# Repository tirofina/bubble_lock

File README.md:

# bubble_lock

Privacy Bubble의 CORE, 정책·MEC·handover·FL·MCP 통합 서비스, ESP32-S3 키링, Raspberry Pi Gateway, 웹 대시보드를 묶은 저장소입니다.

시작 화면에서 사용자 대시보드와 운영 대시보드로 진입합니다. 사용자 화면은 가족·키링 등록, 사건별 위치 공유 승인, 동의·권한 회수, 명령 승인, 알림을 제공합니다. 지도는 GPS/MEC 핀, 위치 정확도 원, 수신기 중심 BLE 추정 원을 표시하며 키링별로 선택할 수 있습니다. 모의 관측과 실제 연결의 출처·관측 시각을 화면에 표시합니다.

## 통합 브랜치

`codex/integrate-all-branches`에서 다음 원격 브랜치의 전체 이력을 통합했습니다. 각 원본은 로컬 추적 브랜치와 `origin/*`에 보관합니다.

| 브랜치 | 원본 커밋 | 구성 |
|---|---|---|
| `main` | `d54a43a` | CORE·중앙 통합 서비스 |
| `PC-MOBIUS-CORE` | `d54a43a` | main과 동일한 CORE 기준 |
| `codex/keyring-namho` | `432a7aa` | 펌웨어·Gateway·PCB·키링 계약 |
| `feature/web-dashboard` | `80ed37f` | 대시보드·SSE·영수증 재생 |

2026-11-10 후속 통합에서 `main`의 `715ef58`, 키링 브랜치의 `686f7b4`까지 반영했습니다. BlueZ 알림 수정과 Feather·Pi 실물 관측 증거를 함께 보존했습니다.

## 설치와 검증

Node.js 22.19 이상, Python 3.11 이상, OpenSSL을 사용합니다. 저장소 루트에서 실행합니다.

```powershell
npm run setup
npm run verify
```

`setup`은 두 Node 패키지와 루트 `.venv`의 Gateway·검증 의존성을 설치합니다. `verify`는 CORE·웹·Gateway 시험, 실제 Node↔Python TLS 1.3/mTLS 교차시험, Edge 프로세스·FL worker 실행, XSD import closure, 계약 검증, oneM2M dry-run, 통합 데모·재생, 웹 빌드를 실행합니다. 결과와 로그 SHA-256은 `.local/verification/verify/results.json`에 저장됩니다. OpenSSL 경로는 `KEYRING_TEST_OPENSSL`, 초기 Python 실행 경로는 `PYTHON`으로 지정할 수 있습니다.

## 실행

```powershell
npm run demo
npm run events
npm run dashboard
```

`events`와 `dashboard`는 각각 터미널에서 실행합니다. 웹 주소는 `http://127.0.0.1:5173`입니다. 중앙 서비스 실행 기록을 보려면 이벤트 서버를 다음과 같이 실행합니다.

- 사용자 지도: `http://127.0.0.1:5173/#/user/map`
- 운영 대시보드: `http://127.0.0.1:5173/#/operator/overview`
- 기본 실행은 명시된 모의 환경입니다. 실제 로그인은 [OIDC 세션 설정](web-dashboard/docs/oidc-session.md), 실제 위치 수신은 [위치 feed](web-dashboard/docs/location-feed.md)와 [정밀 위치 권한](pc-mobius/integration/PORTAL_LOCATION.md)을 따라 연결합니다.

```powershell
$env:RECEIPT_FILE = (Resolve-Path 'pc-mobius/receipts/integration-demo.jsonl').Path
npm run events
```

대시보드는 시작 시 읽은 영수증을 재생합니다. `demo`를 다시 실행한 후 이벤트 서버를 재시작하면 새 기록을 반영합니다.

Gateway용 중앙 API는 [인증서 등록 설정](pc-mobius/config/integration-api.example.json)의 서버·CA 경로, 인증서 SHA-256 지문, 장치·household 매핑을 채운 뒤 실행합니다.

```powershell
$env:PRIVACY_BUBBLE_API_CONFIG = (Resolve-Path '.local/integration-api.json').Path
npm run api
```

설정의 TLS 파일 경로는 `pc-mobius`를 기준으로 해석하므로 절대 경로 사용을 권장합니다. 기본 API 포트는 8787입니다. 인증서 설정을 생략하면 `/healthz` 상태 조회를 제공합니다. API의 인증 주체는 검증된 클라이언트 인증서 또는 서명된 OIDC 토큰과 서버 등록표에서 결정합니다.

## 구성과 연결

- [PC-Mobius](pc-mobius/README.md): oneM2M 자원·MQTT/HTTP·Group/ACK/readback.
- [중앙 통합 서비스](pc-mobius/integration/README.md): consent·grant·명령 승인·MEC·handover·FL·MCP.
- [키링·Gateway](keyring/README.md): BLE 관측·장치 명령·SQLite 큐·TLS 전송.
- [펌웨어](keyring/firmware/README.md): ESP32-S3, 기본/ST7789/JD9853 프로필.
- [웹 대시보드](web-dashboard/README.md): CORE·INTEGRATION 혼합 영수증, 감사 검색, 서비스 상태.
- [통합 계약과 실행 범위](docs/branch-integration.md): 호환 수정, API, 재현 절차.
- [프로젝트 구현 기준](PROJECT_IMPLEMENTATION_RUBRIC_PLAN.md): DOC-REV 2.0.0.
- [전체 개발 완료 기록](docs/development-completion.md): 통합 개발 내용·실행법·검증·인계.
- [ZIP·루브릭 감사](docs/rubric-audit.md): 원본 요구사항·구현·시험 근거.
- [Edge 프로세스 배치](pc-mobius/integration/EDGE_DEPLOYMENT.md): inventory·mTLS·배치·이전·복구.
- [PostgreSQL 정책 정본](pc-mobius/integration/POSTGRES.md): 동시성·이행·재시작.
- [MEC](pc-mobius/integration/MEC.md), [FL](pc-mobius/integration/FL.md), [MCP](pc-mobius/integration/MCP.md): 서비스별 설정과 실행 시험.
- [표준 SDT와 버전 어댑터](pc-mobius/SDT.md): canonical wire·XSD 계보·실제 CSE 교체 시험.

검증은 단위·모의 공급자·실제 로컬 TLS/DB/CSE/프로세스·브라우저·컴파일 범위로 구분합니다. 실물 Pi·키링, 외부 Edge·MEC·ESTIMED·OIDC와 공개 실증은 사용자 지시에 따라 [외부 실증 TODO](docs/external-validation-todo.md)로 관리합니다. 기존 브랜치의 장비·CSE 증거는 각 `evidence/`에 날짜별로 보관합니다.

후속 작업은 [TODO 목록](docs/remaining-todo.md), 최종 실행 결과는 [개발 완료 기록](docs/development-completion.md)에서 확인합니다.

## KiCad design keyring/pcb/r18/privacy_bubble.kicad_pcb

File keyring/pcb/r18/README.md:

# r18-hand-solder 인계용 원본 snapshot

ROLE KEYRING / 남호 · DOC-REV 2.0.0 · source included / unverified.

기존 작업공간 `hardware/privacy_bubble_r18_hand_solder/`의 설계와 의존 파일을 복사했다. 원본은 보존했고 회로·배치·패드·네트·BOM 값을 수정하지 않았다. 이 폴더는 새 제조 release나 현재 펌웨어의 실물 검증 결과가 아니다.

KiCad 10에서 [privacy_bubble.kicad_pro](privacy_bubble.kicad_pro)를 연다. 이번 작업에서는 KiCad를 실행하거나 프로젝트를 열지 않았다. PCB generator_version은10.0이고 과거 README는10.0.3 사용을 기록한다. 다른 버전으로 저장하는 변경은 별도로 관리한다.

| 파일·폴더 | 내용 |
|---|---|
| privacy_bubble.kicad_sch / .kicad_pcb / .kicad_pro / .kicad_dru | 회로도·PCB·프로젝트·기존 custom rule |
| Release.kicad_sym / sym-lib-table | 로컬 심볼과 `${KIPRJMOD}` 경로 |
| HandSolder.pretty / Sourced_4L.pretty / fp-lib-table | 손납땜 변경 및 기존 풋프린트 |
| 3dmodels / sourced_cad/MAX98357A.3dshapes | 원본 로컬 모델 |
| working_data | 기존 reference별·구매용 BOM CSV. 재추출·갱신하지 않음 |
| reference_exports/BOM_PCB_1board.csv | 원래 deliverables의1장 기준 통합표. 발주 파일이 아님 |
| external_parts | 두 LCD·케이스·GPIO·커넥터 표 |
| hand_solder_changes.csv / .json / four_layer_stackup.json | 기존 변경 이력·stackup metadata |
| UPSTREAM_README.md | 원본 README와 과거 검사·hash·수량 기록 |
| source-inventory.json | 복사한222개 파일의 출처·byte 수·SHA256·파일 시각 |

일부 모델은 `${KICAD10_3DMODEL_DIR}`의 설치 라이브러리를 참조하므로 일반 KiCad 라이브러리도 필요하다. 기존 시각화용 대체 모델을 실물 기구 검증 결과로 사용하지 않는다. MAX9850의 정확한 TQFN 모델은 원래 BOM에서도 미확보로 기록한다.

inventory hash는 복사한 byte의 식별 정보다. 분석·build·전기적 검증 결과가 아니다. `.gitattributes`로 이 폴더의 newline 변환을 막았다. 목록에는 원본 복사 파일만 기록하며 이 README 등 새 안내 문서는 제외한다.

원본 README·stackup·BOM 안의 verified/DRC/ERC/simulation/구매 정보는 기존 저자의 과거 기록이다. 이번에 재현·검증·갱신하지 않았으며 현재 firmware의 release 증거로 승격하지 않는다. analysis/Checks·거버·드릴·ZIP·editor 상태·중복 미사용 library는 가져오지 않았고 원래 작업공간에 보존했다.

BOM은 기존 export이며 현재 가격·재고·공급사 번호를 확인한 표가 아니다. GPIO prose 일부가 오래됐으므로 [핀 정정·펌웨어 연결](../HARDWARE_FIRMWARE_MAP.md)을 먼저 따른다. 부품 재선정·제조 발주를 하지 않았다.

원본 property·model 명칭·source URL을 유지했다. KiCad 유래 library data의 원저자는 KiCad community다. HandSolder 변경은 기존 변경 이력에 남아 있다. [KiCad 공식 license](https://www.kicad.org/libraries/license/)와 [CC BY-SA4.0](https://creativecommons.org/licenses/by-sa/4.0/) 및 KiCad 설계 예외를 참고한다. KiCad 유래 library collection 부분의 attribution/license를 유지하며 supplier 모델이나 프로젝트 전체에 일괄 새 라이선스를 부여하지 않는다. MAX98357A/EasyEDA/supplier 표기 모델은 받은 project asset과 해당 출처 조건을 유지한다.

실제 조립 revision·배터리/화면/모터·스피커·전력/RF/열/조립 검사·flash·통합 시연은 별도 미완료다.

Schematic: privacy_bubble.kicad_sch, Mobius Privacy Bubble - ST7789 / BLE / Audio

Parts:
C1: 1uF 10V X7R; C_0603_1608Metric_Pad1.08x0.95mm_HandSolder_C1_HandSolder; MPN GRM188R71A105KA61D
C2: 10uF 10V X7R; C_0805_2012Metric_Pad1.18x1.45mm_HandSolder_C2_HandSolder; MPN GRM21BR71A106KE51L
C3: 100nF 50V X7R; C_0603_1608Metric_Pad1.08x0.95mm_HandSolder_C3_HandSolder; MPN C1608X7R1H104K080AA
C4: 4.7uF 10V X7R; C_0805_2012Metric_Pad1.18x1.45mm_HandSolder_C4_HandSolder; MPN GRM21BR71A475KA73L
C5: 10uF 10V X7R; C_0805_2012Metric_Pad1.18x1.45mm_HandSolder_C5_HandSolder; MPN GRM21BR71A106KE51L
C6: 4.7uF 10V X7R; C_0805_2012Metric_Pad1.18x1.45mm_HandSolder_C6_HandSolder; MPN GRM21BR71A475KA73L
C7: 100nF 50V X7R; Capacitor_SMD_C_0603_1608Metric; MPN C1608X7R1H104K080AA
C8: 10uF 10V X7R; C_0805_2012Metric_Pad1.18x1.45mm_HandSolder_C8_HandSolder; MPN GRM21BR71A106KE51L
C9: 22uF 16V X5R; C_0805_2012Metric_Pad1.18x1.45mm_HandSolder_C9_HandSolder; MPN GRM21BR61C226ME44L
C10: 22uF 16V X5R; C_0805_2012Metric_Pad1.18x1.45mm_HandSolder_C10_HandSolder; MPN GRM21BR61C226ME44L
C15: 100nF 50V X7R; C_0402_1005Metric_Pad0.74x0.62mm_HandSolder_C15_HandSolder; MPN GRM155R71H104KE14D
C16: 100nF 50V X7R; C_0402_1005Metric_Pad0.74x0.62mm_HandSolder_C16_HandSolder; MPN GRM155R71H104KE14D
C17: 10uF 10V X5R 20%; C_0603_1608Metric_Pad1.08x0.95mm_HandSolder_C17_HandSolder; MPN GRM188R61A106ME69D
C18: 100nF 50V X7R; C_0603_1608Metric_Pad1.08x0.95mm_HandSolder_C18_HandSolder; MPN C1608X7R1H104K080AA
C19: 10uF 10V X7R; C_0805_2012Metric_Pad1.18x1.45mm_HandSolder_C19_HandSolder; MPN GRM21BR71A106KE51L
C20: 100nF 50V X7R; C_0402_1005Metric_Pad0.74x0.62mm_HandSolder_C20_HandSolder; MPN GRM155R71H104KE14D
C21: 100nF 50V X7R; C_0603_1608Metric_Pad1.08x0.95mm_HandSolder_C21_HandSolder; MPN C1608X7R1H104K080AA
C22: 10uF 10V X7R; C_0805_2012Metric_Pad1.18x1.45mm_HandSolder_C22_HandSolder; MPN GRM21BR71A106KE51L
C23, C49: 10uF 10V X7R; Capacitor_SMD_C_0805_2012Metric; MPN GRM21BR71A106KE51L
C24: 100nF 50V X7R; C_0402_1005Metric_Pad0.74x0.62mm_HandSolder_C24_HandSolder; MPN C1005X7R1H104K050BB
C25: 100nF 50V X7R; C_0402_1005Metric_Pad0.74x0.62mm_HandSolder_C25_HandSolder; MPN C1005X7R1H104K050BB
C26: 100nF 50V X7R; C_0402_1005Metric_Pad0.74x0.62mm_HandSolder_C26_HandSolder; MPN C1005X7R1H104K050BB
C27: 100nF 50V X7R; C_0402_1005Metric_Pad0.74x0.62mm_HandSolder_C27_HandSolder; MPN GRM155R71H104KE14D
C28: 10uF 10V X7R; C_0805_2012Metric_Pad1.18x1.45mm_HandSolder_C28_HandSolder; MPN GRM21BR71A106KE51L
C29: 100nF 50V X7R; C_0402_1005Metric_Pad0.74x0.62mm_HandSolder_C29_HandSolder; MPN GRM155R71H104KE14D
C30: 4.7nF 50V X7R 10%; C_0402_1005Metric; MPN GRM155R71H472KA01D
C31: 1nF 50V C0G; C_0402_1005Metric_Pad0.74x0.62mm_HandSolder_C31_HandSolder; MPN GRM1555C1H102JA01D
C32: 100nF 50V X7R; C_0402_1005Metric_Pad0.74x0.62mm_HandSolder_C32_HandSolder; MPN GRM155R71H104KE14D
C33: 22uF 16V X5R; C_0805_2012Metric_Pad1.18x1.45mm_HandSolder_C33_HandSolder; MPN GRM21BR61C226ME44L
C35: 100nF 50V X7R; C_0402_1005Metric_Pad0.74x0.62mm_HandSolder_C35_HandSolder; MPN GRM155R71H104KE14D
C36: 100nF 50V X7R; C_0402_1005Metric_Pad0.74x0.62mm_HandSolder_C36_HandSolder; MPN GRM155R71H104KE14D
C37: 330uF 6.3V polymer; CP_EIA-7343-31_Kemet-D_C37_HandSolder; MPN T520D337M006ATE025
C38: 1uF 10V X5R; C_0402_1005Metric_Pad0.74x0.62mm_HandSolder_C38_HandSolder; MPN CL05A105KP5NNNC
C39: 1uF 10V X5R; C_0402_1005Metric_Pad0.74x0.62mm_HandSolder_C39_HandSolder; MPN CL05A105KP5NNNC
C40: 1uF 10V X5R; C_0402_1005Metric_Pad0.74x0.62mm_HandSolder_C40_HandSolder; MPN CL05A105KP5NNNC
C41: 1uF 10V X5R; C_0402_1005Metric_Pad0.74x0.62mm_HandSolder_C41_HandSolder; MPN CL05A105KP5NNNC
C42: 1uF 10V X5R; C_0402_1005Metric_Pad0.74x0.62mm_HandSolder_C42_HandSolder; MPN CL05A105KP5NNNC
C43: 1uF 10V X5R; C_0402_1005Metric_Pad0.74x0.62mm_HandSolder_C43_HandSolder; MPN CL05A105KP5NNNC
C44: 470nF 10V X5R; C_0402_1005Metric; MPN GRM155R61A474KE15D
C45: 2.2uF 10V X5R; C_0603_1608Metric; MPN CL10A225KP8NNNC
C46: 680uF 6.3V polymer; CP_EIA-7343-43_Kemet-X_C46_HandSolder; MPN T530X687M006ATE010
C47: 680uF 6.3V polymer; CP_EIA-7343-43_Kemet-X_C47_HandSolder; MPN T530X687M006ATE010
C48: 100nF 50V X7R; C_0402_1005Metric_Pad0.74x0.62mm_HandSolder_C48_HandSolder; MPN GRM155R71H104KE14D
C50: 470uF 6.3V polymer; CP_EIA-7343-31_Kemet-D_C50_HandSolder; MPN T520D477M006ATE025
D1: PMEG2010ER flyback; D_Diode_SMD_Nexperia_CFP3_SOD-123W_D1_HandSolder; MPN PMEG2010ER,115
D2: CHARGE LED; LED_0603_1608Metric_Pad1.05x0.95mm_HandSolder_D2_HandSolder; MPN LTST-C190KRKT
J1: USB-C USB2.0; USB_C_Receptacle_HRO_TYPE-C-31-M-12_J1_HandSolder; MPN TYPE-C-31-M-12
J2: BATTERY DTP803040; Connector_JST_JST_PH_S2B-PH-SM4-TB_1x02-1MP_P2.00mm_Horizon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; MPN S2B-PH-SM4-TB(LF)(SN)
J3: ST7789 HARNESS; Connector_JST_JST_SH_SM08B-SRSS-TB_1x08_1MP_P1.00mm_Horizon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; MPN SM08B-SRSS-TB(LF)(SN)
J4: SPEAKER WIRE SOLDER; SolderWire-0.1sqmm_1x02_P3.6mm_D0.4mm_OD1mm
J5: NTC DIRECT SOLDER; SolderWire-0.1sqmm_1x02_P3.6mm_D0.4mm_OD1mm
J6: MOTOR WIRE SOLDER; SolderWire-0.5sqmm_1x02_P4.6mm_D0.9mm_OD2.1mm
J7: UART DEBUG; DebugPads_1x04_P1.27; not fitted
J9: POWER SWITCH WIRES; Connector_Wire_SolderWire-0.127sqmm_1x03_P3.7mm_D0.48mm_OD1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
J10: microSD DM3AT-SF-PEJM5; microSD_HC_Hirose_DM3AT-SF-PEJM5_J10_HandSolder; MPN DM3AT-SF-PEJM5
J11: 3.5mm stereo output; AUDIO-SMD_PJ-320D; MPN PJ-320D-4A
L1: 2.2uH XFL4020; Inductor_SMD_L_Coilcraft_XxL4020_L1_HandSolder; MPN XFL4020-222MEC
NT1: AGND STAR; NetTie_NetTie-2_SMD_Pad0.5mm
NT2: HEADPHONE ANALOG STAR; NetTie-2_SMD_Pad0.5mm; MPN PCB copper
Q1: AO3400A; SOT-23_Handsoldering_Q1_HandSolder; MPN AO3400A
Q2: 2N7002; SOT-23_Handsoldering_Q2_HandSolder; MPN 2N7002
Q3: AO3401A; SOT-23_Handsoldering_Q3_HandSolder; MPN AO3401A
Q4: 2N7002; SOT-23_Handsoldering_Q4_HandSolder; MPN 2N7002
R1: 100k 1%; R_0402_1005Metric_Pad0.72x0.64mm_HandSolder_R1_HandSolder; MPN RC0402FR-07100KL
R2: 10k 1%; R_0402_1005Metric_Pad0.72x0.64mm_HandSolder_R2_HandSolder; MPN RC0402FR-0710KL
R3: 4.7k 1%; R_0402_1005Metric_Pad0.72x0.64mm_HandSolder_R3_HandSolder; MPN RC0402FR-074K7L
R4: 4.7k 1%; R_0402_1005Metric_Pad0.72x0.64mm_HandSolder_R4_HandSolder; MPN RC0402FR-074K7L
R5: 47k 1%; R_0402_1005Metric_Pad0.72x0.64mm_HandSolder_R5_HandSolder; MPN RC0402FR-0747KL
R6: 47k 1%; R_0402_1005Metric_Pad0.72x0.64mm_HandSolder_R6_HandSolder; MPN RC0402FR-0747KL
R7: 5.1k 1%; R_0402_1005Metric_Pad0.72x0.64mm_HandSolder_R7_HandSolder; MPN RC0402FR-075K1L
R8: 5.1k 1%; R_0402_1005Metric_Pad0.72x0.64mm_HandSolder_R8_HandSolder; MPN RC0402FR-075K1L
R9: 33R 1%; R_0402_1005Metric_Pad0.72x0.64mm_HandSolder_R9_HandSolder; MPN RC0402FR-0733RL
R10: 33R 1%; R_0402_1005Metric_Pad0.72x0.64mm_HandSolder_R10_HandSolder; MPN RC0402FR-0733RL
R11: 100k 1%; R_0402_1005Metric_Pad0.72x0.64mm_HandSolder_R11_HandSolder; MPN RC0402FR-07100KL
R12: 4.53k 1%; R_0402_1005Metric_Pad0.72x0.64mm_HandSolder_R12_HandSolder; MPN RC0402FR-074K53L
R13: 3.57k 1%; R_0402_1005Metric_Pad0.72x0.64mm_HandSolder_R13_HandSolder; MPN RC0402FR-073K57L
R14: 1.50k 1%; R_0402_1005Metric_Pad0.72x0.64mm_HandSolder_R14_HandSolder; MPN RC0402FR-071K5L
R15: 69.8k 1%; R_0402_1005Metric_Pad0.72x0.64mm_HandSolder_R15_HandSolder; MPN RC0402FR-0769K8L
R18: 2.2k 1%; R_0402_1005Metric_Pad0.72x0.64mm_HandSolder_R18_HandSolder; MPN RC0402FR-072K2L
R19: 100R 1%; R_0402_1005Metric_Pad0.72x0.64mm_HandSolder_R19_HandSolder; MPN RC0402FR-07100RL
R20: 10k 1%; R_0402_1005Metric_Pad0.72x0.64mm_HandSolder_R20_HandSolder; MPN RC0402FR-0710KL
R31: 33R 1%; R_0402_1005Metric_Pad0.72x0.64mm_HandSolder_R31_HandSolder; MPN RC0402FR-0733RL
R32: 33R 1%; R_0402_1005Metric_Pad0.72x0.64mm_HandSolder_R32_HandSolder; MPN RC0402FR-0733RL
R33: 47k 1%; R_0402_1005Metric_Pad0.72x0.64mm_HandSolder_R33_HandSolder; MPN RC0402FR-0747KL
R34: 47k 1%; R_0402_1005Metric_Pad0.72x0.64mm_HandSolder_R34_HandSolder; MPN RC0402FR-0747KL
R35: 100k 1%; Resistor_SMD_R_0402_1005Metric; MPN RC0402FR-07100KL
R36: 33R 1%; R_0402_1005Metric_Pad0.72x0.64mm_HandSolder_R36_HandSolder; MPN RC0402FR-0733RL
R37: 33R 1%; R_0402_1005Metric_Pad0.72x0.64mm_HandSolder_R37_HandSolder; MPN RC0402FR-0733RL
R38: 33R 1%; R_0402_1005Metric_Pad0.72x0.64mm_HandSolder_R38_HandSolder; MPN RC0402FR-0733RL
R39: 100k 1%; R_0402_1005Metric_Pad0.72x0.64mm_HandSolder_R39_HandSolder; MPN RC0402FR-07100KL
R40: 100k 1%; R_0402_1005Metric_Pad0.72x0.64mm_HandSolder_R40_HandSolder; MPN RC0402FR-07100KL
R41: 100R 1%; R_0402_1005Metric_Pad0.72x0.64mm_HandSolder_R41_HandSolder; MPN RC0402FR-07100RL
R42: 100k 1%; R_0402_1005Metric_Pad0.72x0.64mm_HandSolder_R42_HandSolder; MPN RC0402FR-07100KL
R43: 100k 1%; R_0402_1005Metric_Pad0.72x0.64mm_HandSolder_R43_HandSolder; MPN RC0402FR-07100KL
R44: 100k 1%; R_0402_1005Metric_Pad0.72x0.64mm_HandSolder_R44_HandSolder; MPN RC0402FR-07100KL
R45, R46: 1M 1%; Resistor_SMD_R_0402_1005Metric; MPN RC0402FR-071ML
R47: 560k 1%; R_0402_1005Metric_Pad0.72x0.64mm_HandSolder_R47_HandSolder; MPN RC0402FR-07560KL
R48: 47k 1%; R_0402_1005Metric_Pad0.72x0.64mm_HandSolder_R48_HandSolder; MPN RC0402FR-0747KL
R49: 100k 1%; R_0402_1005Metric_Pad0.72x0.64mm_HandSolder_R49_HandSolder; MPN RC0402FR-07100KL
R50: 100k 1%; R_0402_1005Metric_Pad0.72x0.64mm_HandSolder_R50_HandSolder; MPN RC0402FR-07100KL
R51: 100k 1%; R_0402_1005Metric_Pad0.72x0.64mm_HandSolder_R51_HandSolder; MPN RC0402FR-07100KL
R52: 61.9k 1%; R_0402_1005Metric_Pad0.72x0.64mm_HandSolder_R52_HandSolder; MPN RC0402FR-0761K9L
R53: 100k 1%; R_0402_1005Metric_Pad0.72x0.64mm_HandSolder_R53_HandSolder; MPN RC0402FR-07100KL
R54: 57.6k 1%; R_0402_1005Metric_Pad0.72x0.64mm_HandSolder_R54_HandSolder; MPN RC0402FR-0757K6L
R55: 1M 1%; R_0402_1005Metric_Pad0.72x0.64mm_HandSolder_R55_HandSolder; MPN RC0402FR-071ML
R56: 100k 1%; R_0402_1005Metric_Pad0.72x0.64mm_HandSolder_R56_HandSolder; MPN RC0402FR-07100KL
R57: 100k 1%; R_0402_1005Metric_Pad0.72x0.64mm_HandSolder_R57_HandSolder; MPN RC0402FR-07100KL
R58: 100k 1%; R_0402_1005Metric; MPN RC0402FR-07100KL
R59: 133k 1%; R_0402_1005Metric; MPN RC0402FR-07133KL
R60: 100R 1% 0.5W; R_0805_2012Metric_Pad1.20x1.40mm_HandSolder_R60_HandSolder; MPN ERJP06F1000V
R61: 0.1R 1% 0.125W; R_0805_2012Metric_Pad1.20x1.40mm_HandSolder_R61_HandSolder; MPN RL0805FR-070R1L
R62: 100k 1%; R_0402_1005Metric_Pad0.72x0.64mm_HandSolder_R62_HandSolder; MPN RC0402FR-07100KL
R63: 47k 1%; R_0402_1005Metric_Pad0.72x0.64mm_HandSolder_R63_HandSolder; MPN RC0402FR-0747KL
R64: 47k 1%; R_0402_1005Metric_Pad0.72x0.64mm_HandSolder_R64_HandSolder; MPN RC0402FR-0747KL
R65: 47k 1%; R_0402_1005Metric_Pad0.72x0.64mm_HandSolder_R65_HandSolder; MPN RC0402FR-0747KL
R66: 47k 1%; R_0402_1005Metric_Pad0.72x0.64mm_HandSolder_R66_HandSolder; MPN RC0402FR-0747KL
R67: 47k 1%; R_0402_1005Metric_Pad0.72x0.64mm_HandSolder_R67_HandSolder; MPN RC0402FR-0747KL
R68: 33R 1%; R_0402_1005Metric_Pad0.72x0.64mm_HandSolder_R68_HandSolder; MPN RC0402FR-0733RL
R69: 220R 1%; R_0603_1608Metric_Pad0.98x0.95mm_HandSolder_R69_HandSolder; MPN RC0603FR-07220RL
R71: 0R jumper; R_0805_2012Metric_Pad1.20x1.40mm_HandSolder_R71_HandSolder; MPN RC0805JR-070RL
SW1: PANIC; Button_Switch_SMD_SW_SPST_PTS810; MPN PTS810SJK250SMTRLFS
SW2: CONFIRM; Button_Switch_SMD_SW_SPST_PTS810; MPN PTS810SJK250SMTRLFS
SW3: RESET; Button_Switch_SMD_SW_SPST_B3U-1000P; MPN B3U-1000P
SW4: BOOT; Button_Switch_SMD_SW_SPST_PTS810; MPN PTS810SJK250SMTRLFS
TP1: VBUS; TestPoint_TestPoint_Pad_D1.0mm
TP2: VBAT; TestPoint_TestPoint_Pad_D1.0mm
TP3: SYS; TestPoint_TestPoint_Pad_D1.0mm
TP4: +3V3; TestPoint_TestPoint_Pad_D1.0mm
TP5: GND; TestPoint_TestPoint_Pad_D1.0mm
TP6: PGOOD_N; TestPoint_TestPoint_Pad_D1.0mm
TP7: CHG_N; TestPoint_TestPoint_Pad_D1.0mm
U1: ESP32-S3-WROOM-1-N16R8; RF_Module_ESP32-S3-WROOM-1_JLC030; MPN ESP32-S3-WROOM-1-N16R8
U3: BQ24074RGTR; Package_DFN_QFN_VQFN-16-1EP_3x3mm_P0.5mm_EP1.6x1.6mm; MPN BQ24074RGTR
U4: TPS63001DRCR; Package_SON_Texas_DRC0010J_ThermalVias_JLC030; MPN TPS63001DRCR
U6: LIS2DW12TR; Package_LGA_LGA-12_2x2mm_P0.5mm; MPN LIS2DW12TR
U7: MAX17048G+; Package_DFN_QFN_TDFN-8-1EP_2x2mm_P0.5mm_EP0.8x1.2mm; MPN MAX17048G+
U8: MAX98357AETE+; Package_DFN_QFN_TQFN-16-1EP_3x3mm_P0.5mm_EP1.23x1.23mm; MPN MAX98357AETE+
U9: USBLC6-2SC6; SOT-23-6_Handsoldering_U9_HandSolder; MPN USBLC6-2SC6
U10: TLV6700DDCR; SOT-23-6_Handsoldering_U10_HandSolder; MPN TLV6700DDCR
U11: TPS2553DBVR; SOT-23-6_Handsoldering_U11_HandSolder; MPN TPS2553DBVR
U12: TLV3012BIDBVR; SOT-23-6_Handsoldering_U12_HandSolder; MPN TLV3012BIDBVR
U13: TPS2553DBVR; SOT-23-6_Handsoldering_U13_HandSolder; MPN TPS2553DBVR
U15: INA219BIDCNR; SOT-23-8_Handsoldering_U15_HandSolder; MPN INA219BIDCNR
U16: MAX9850ETI+; TQFN-28-1EP_5x5mm_P0.5mm_EP3.25x3.25mm; MPN MAX9850ETI+
U17: TPS3839G18DBZR; SOT-23_Handsoldering_U17_HandSolder; MPN TPS3839G18DBZR

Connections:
/+3V3: C2.1, C3.1, C15.1, C16.1, C17.1, C19.1, C20.1, C32.1, C35.1, C36.1, C37.1, C38.1, C39.1, C40.1, C49.1, J3.1, J7.1, J10.4 (VDD), R1.1, R2.1, R3.1, R4.1, R5.1, R6.1, R33.1, R34.1, R56.1, R57.1, R61.2, R63.2, R64.2, R65.2, R66.2, R67.2, TP4.1, U1.2 (3V3), U6.2 (CS), U6.3 (SA0), U6.9 (VDD), U6.10 (VDDIO), U13.1 (IN), U15.2 (IN-), U15.4 (VS), U16.4 (DVDD), U16.17 (AVDD), U16.26 (PVDD)
/ACCEL_INT: U1.10 (IO17), U6.12 (INT1)
/AMP_EN: Q4.3 (D), R39.1, U8.4 (SD_MODE)
/AMP_GAIN: R40.2, U8.2 (GAIN_SLOT)
/AMP_GATE: Q4.1 (G), R62.1, U1.9 (IO16)
/AUX3V3: C21.1, C22.1, C23.1, C33.1, D1.1 (K), J6.1, Q3.2 (S), R35.2, R39.2, R40.1, U8.7 (VDD), U8.8 (VDD), U13.6 (OUT)
/AUX_EN: R58.1, U1.4 (IO4), U13.3 (EN)
/AUX_FAULT_N: R57.2, U13.4 (~FAULT)
/AUX_ILIM: R59.1, U13.5 (ILIM)
/BAT_TS: J5.1, R44.1, R46.1, U3.1 (TS)
/BOOT0: R2.2, SW4.1, U1.27 (IO0)
/BTN_CONFIRM: R6.2, SW2.1, U1.6 (IO6)
/BTN_PANIC: R5.2, SW1.1, U1.7 (IO7)
/CHG_DISABLE: Q2.3 (D), R49.2, U3.4 (~CE)
/CHG_ILIM: R13.1, U3.12 (ILIM)
/CHG_ISET: R12.1, U3.16 (ISET)
/CHG_ITERM: R14.1, U3.15 (ITERM)
/CHG_LED_A: D2.2 (A), R18.2
/CHG_N: D2.1 (K), TP7.1, U3.9 (~CHG)
/CHG_TMR: R15.1, U3.14 (TMR)
/GND: C1.2, C2.2, C3.2, C4.2, C5.2, C6.2, C8.2, C9.2, C10.2, C15.2, C16.2, C17.2, C18.2, C19.2, C20.2, C21.2, C22.2, C23.2, C24.2, C25.2, C26.2, C27.2, C28.2, C29.2, C30.2, C31.2, C32.2, C33.2, C35.2, C36.2, C37.2, C38.2, C40.2, C45.2, C46.2, C47.2, C48.2, C49.2, C50.2, J1.A1 (GND), J1.A12 (GND), J1.B1 (GND), J1.B12 (GND), J1.SH (SHIELD), J2.2, J3.2, J5.2, J7.2, J9.3, J10.6 (VSS), J10.SH (SHIELD), NT1.2, NT2.2, Q1.2 (S), Q2.2 (S), Q4.2 (S), R7.2, R8.2, R11.2, R12.2, R13.2, R14.2, R15.2, R42.2, R43.2, R45.2, R47.2, R50.2, R51.2, R52.2, R54.2, R58.2, R59.2, R62.2, SW1.2, SW2.2, SW3.2, SW4.2, TP5.1, U1.1 (GND), U1.40 (GND), U1.41 (GND), U3.8 (VSS), U3.17 (VSS), U4.3 (PGND), U4.7 (PS/SYNC), U4.11 (PGND), U6.6 (GND), U6.7 (RES_GND), U6.8 (GND), U7.1 (CTG), U7.4 (GND), U7.6 (QSTRT), U7.9 (EP_GND), U8.3 (GND), U8.11 (GND), U8.15 (GND), U8.17 (EP_GND), U9.2 (GND), U10.2 (GND), U11.2 (GND), U12.2 (V-), U13.2 (GND), U15.3 (GND), U15.7 (A0), U15.8 (A1), U16.6 (DGND), U16.7 (ADD), U16.24 (PGND), U17.1 (GND)
/HP_AGND: C39.2, C41.2, C42.2, C43.2, J11.1, J11.2, NT2.1, U16.9 (INR), U16.10 (INL), U16.14 (AGND), U16.29 (AGND)
/HP_C1N: C44.2, U16.23 (C1N)
/HP_C1P: C44.1, U16.25 (C1P)
/HP_L: J11.4, U16.19 (HPL)
/HP_MCLK: R68.2, U16.5 (MCLK)
/HP_MCLK_RAW: R68.1, U1.21 (IO13)
/HP_NREG: C42.1, U16.15 (NREG)
/HP_PREG: C43.1, U16.16 (PREG)
/HP_PVSS: C45.1, U16.20 (SVSS), U16.22 (PVSS)
/HP_R: J11.3, U16.18 (HPR)
/HP_REF: C41.1, U16.13 (REF)
/I2C_SCL: R4.2, U1.23 (IO21), U6.1 (SCL), U7.7 (SCL), U15.5 (SCL), U16.27 (SCL)
/I2C_SDA: R3.2, U1.22 (IO14), U6.4 (SDA), U7.8 (SDA), U15.6 (SDA), U16.28 (SDA)
/I2S_BCLK: R36.2, U8.16 (BCLK), U16.2 (BCLK)
/I2S_BCLK_RAW: R36.1, U1.34 (IO41)
/I2S_DOUT: R38.2, U8.1 (DIN), U16.3 (SDIN)
/I2S_DOUT_RAW: R38.1, U1.35 (IO42)
/I2S_LRCLK: R37.2, U8.14 (LRCLK), U16.1 (LRCLK)
/I2S_LRCLK_RAW: R37.1, U1.33 (IO40)
/LCD_BL_PWM: Q3.1 (G), R35.1, U1.38 (IO2)
/LCD_BL_RAW: Q3.3 (D), R60.1
/LCD_BL_SUPPLY: J3.8, R60.2
/LCD_CS: J3.5, R33.2, U1.11 (IO18)
/LCD_DC: R71.1, U1.12 (IO8)
/LCD_DC_BRIDGE: J3.6, R71.2
/LCD_MOSI: J3.3, J10.3 (CMD), R32.2, R65.1
/LCD_MOSI_RAW: R32.1, U1.31 (IO38)
/LCD_RST: J3.7, R34.2, R69.2
/LCD_SCK: J3.4, J10.5 (CLK), R31.2
/LCD_SCK_RAW: R31.1, U1.32 (IO39)
/MAIN_FAULT_N: R56.2, U1.39 (IO1), U11.4 (~FAULT)
/MAIN_ILIM: R52.1, U11.5 (ILIM)
/MCU_EN: C1.1, R1.2, SW3.1, U1.3 (EN)
/PGOOD_N: TP6.1, U3.7 (~PGOOD)
/PWR_SW: J9.1, R20.2
/REG_AGND: C7.2, NT1.1, U4.9 (GND)
/REG_EN: C24.1, J9.2, R43.1, U11.3 (EN)
/REG_READY: U4.6 (EN), U17.2 (~RESET)
/SD_CS: J10.2 (DAT3/CD), R63.1, U1.18 (IO10)
/SD_DAT1_PULL: J10.8 (DAT1), R66.1
/SD_DAT2_PULL: J10.1 (DAT2), R67.1
/SD_MISO: J10.7 (DAT0), R64.1, U1.19 (IO11)
/SPK_N: J4.2, U8.10 (OUTN)
/SPK_P: J4.1, U8.9 (OUTP)
/SW_L1: L1.1, U4.4 (L1)
/SW_L2: L1.2, U4.2 (L2)
/SYS: C5.1, C27.1, C29.1, R53.1, TP3.1, U3.10 (OUT), U3.11 (OUT), U11.1 (IN), U12.6 (V+)
/SYS_LIMIT: C8.1, C28.1, C46.1, C47.1, C48.1, C50.1, R19.1, U4.5 (VIN), U11.6 (OUT), U17.3 (VDD)
/TEMP_COLD_SENSE: R46.2, R47.1, U10.4 (INB-)
/TEMP_HOT_SENSE: R44.2, R45.1, U10.3 (INA+)
/TEMP_OK: Q2.1 (G), R48.2, R50.1, U10.1 (OUTA), U10.6 (OUTB)
/UART_RX: J7.4, U1.36 (RXD0)
/UART_TX: J7.3, R69.1, U1.37 (TXD0)
/USB_500_EN: R11.1, U1.24 (IO47), U3.6 (EN1)
/USB_CC1: J1.A5 (CC1), R7.1
/USB_CC2: J1.B5 (CC2), R8.1
/USB_DM: J1.A7 (D-), J1.B7 (D-), R9.1, U9.3 (I/O2), U9.4 (I/O2)
/USB_DM_MCU: R9.2, U1.13 (USB_D-)
/USB_DP: J1.A6 (D+), J1.B6 (D+), R10.1, U9.1 (I/O1), U9.6 (I/O1)
/USB_DP_MCU: R10.2, U1.14 (USB_D+)
/USB_LIMIT_EN2: R51.1, U1.17 (IO9), U3.5 (EN2)
/UVLO_OK: R20.1, R55.1, U12.1 (OUT)
/UVLO_REF: C30.1, U12.4 (IN-), U12.5 (REF)
/UVLO_SENSE: C31.1, R53.2, R54.1, R55.2, U12.3 (IN+)
/VBAT: C6.1, C18.1, J2.1, R18.1, TP2.1, U3.2 (BAT), U3.3 (BAT), U7.2 (CELL), U7.3 (VDD)
/VBUS: C4.1, C25.1, C26.1, J1.A4 (VBUS), J1.A9 (VBUS), J1.B4 (VBUS), J1.B9 (VBUS), R48.1, R49.1, TP1.1, U3.13 (IN), U9.5 (VBUS), U10.5 (VDD)
/VIB_GATE: Q1.1 (G), R41.2, R42.1
/VIB_LOW: D1.2 (A), J6.2, Q1.3 (D)
/VIB_PWM: R41.1, U1.15 (IO3)
/VINA: C7.1, R19.2, U4.8 (VINA)
/VREG3V3: C9.1, C10.1, R61.1, U4.1 (VOUT), U4.10 (FB), U15.1 (IN+)

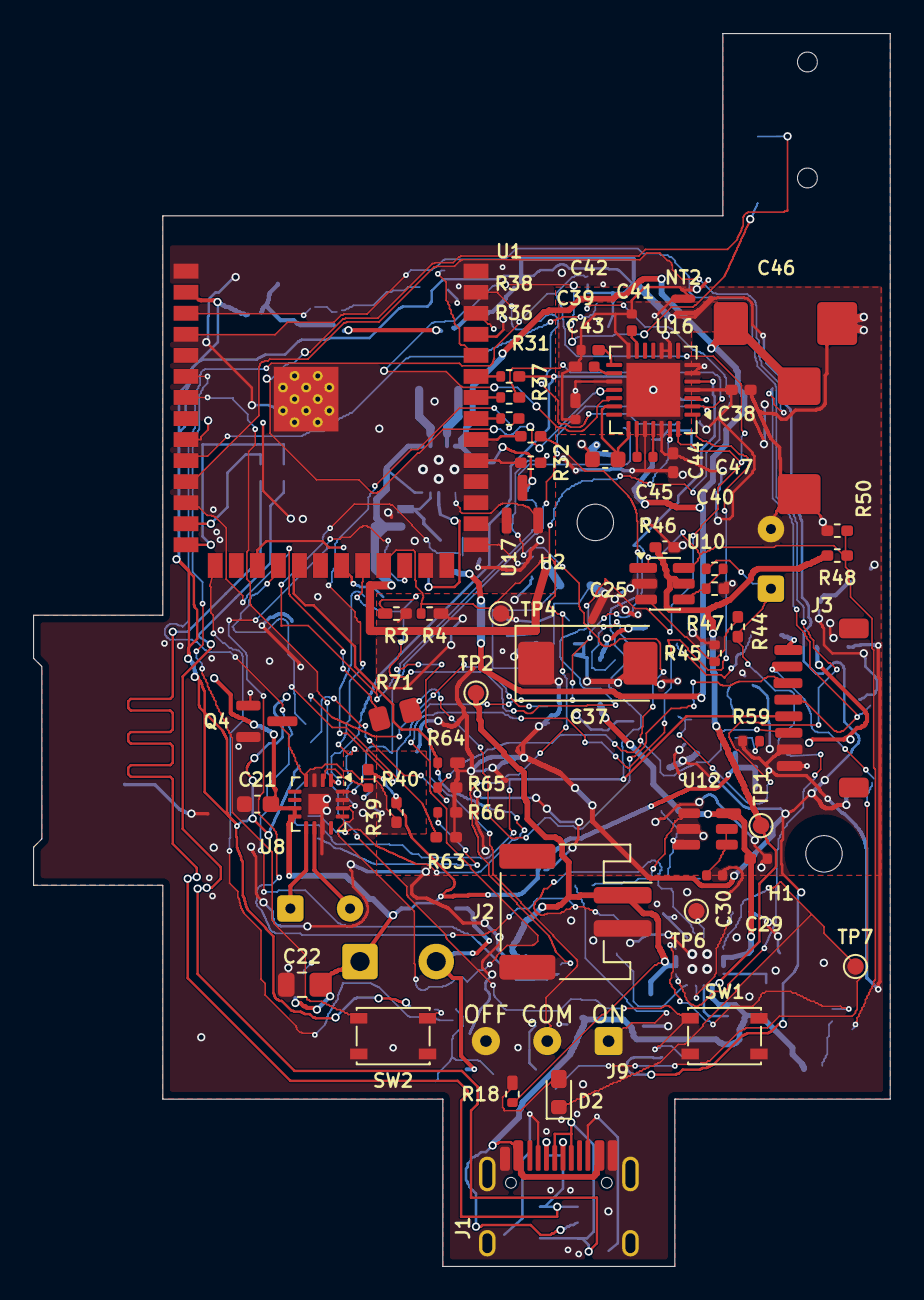
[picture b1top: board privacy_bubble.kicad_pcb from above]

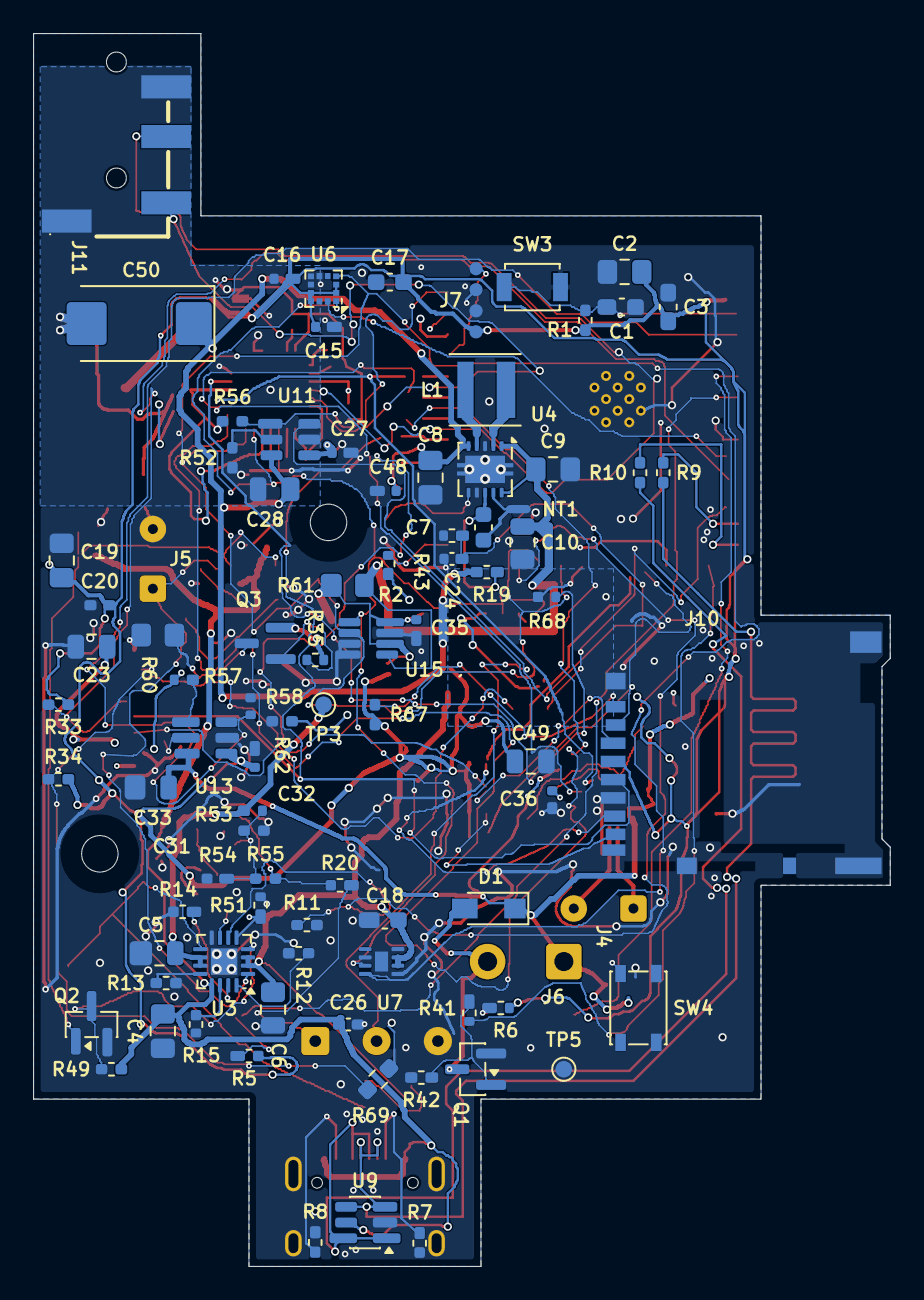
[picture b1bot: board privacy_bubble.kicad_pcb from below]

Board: 4 copper layers, 51.7 x 74.4 mm, 149 parts (89 on the bottom side), 92 nets.

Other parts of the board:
H1, H2: M2 / NPTH 2.2mm; MountingHole_2.2mm_M2

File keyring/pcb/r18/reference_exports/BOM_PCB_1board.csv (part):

MPN,Manufacturer,Quantity_per_PCB,References,Value,Footprints,Sides,Datasheet
GRM188R71A105KA61D,Murata,1,C1,1uF 10V X7R,HandSolder:C_0603_1608Metric_Pad1.08x0.95mm_HandSolder_C1_HandSolder,B,https://www.murata.com/en-global/products/productdetail?part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
GRM21BR71A106KE51L,Murata,8,C2 C5 C8 C19 C22 C23 C49 C28,10uF 10V X7R,HandSolder:C_0805_2012Metric_Pad1.18x1.45mm_HandSolder_C2_HandSolder | HandSolder:C_0805_2012Metric_Pad1.18x1.45mm_HandSolder_C5_HandSolder | HandSolder:C_0805_2012Metric_Pad1.18x1.45mm_HandSolder_C8_HandSolder | HandSolder:C_0805_2012Metric_Pad1.18x1.45mm_HandSolder_C19_HandSolder | HandSolder:C_0805_2012Metric_Pad1.18x1.45mm_HandSolder_C22_HandSolder | Sourced:Capacitor_SMD_C_0805_2012Metric | HandSolder:C_0805_2012Metric_Pad1.18x1.45mm_HandSolder_C28_HandSolder,B | F,https://www.murata.com/en-global/products/productdetail?part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 | https://www.murata.com/
C1608X7R1H104K080AA,TDK,4,C3 C7 C18 C21,100nF 50V X7R,HandSolder:C_0603_1608Metric_Pad1.08x0.95mm_HandSolder_C3_HandSolder | Sourced:Capacitor_SMD_C_0603_1608Metric | HandSolder:C_0603_1608Metric_Pad1.08x0.95mm_HandSolder_C18_HandSolder | HandSolder:C_0603_1608Metric_Pad1.08x0.95mm_HandSolder_C21_HandSolder,B | F,https://product.tdk.com/en/search/capacitor/ceramic/mlcc/inf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
GRM21BR71A475KA73L,Murata,2,C4 C6,4.7uF 10V X7R,HandSolder:C_0805_2012Metric_Pad1.18x1.45mm_HandSolder_C4_HandSolder | HandSolder:C_0805_2012Metric_Pad1.18x1.45mm_HandSolder_C6_HandSolder,B,https://www.murata.com/en-global/products/productdetail?part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
GRM21BR61C226ME44L,Murata,3,C9 C10 C33,22uF 16V X5R,HandSolder:C_0805_2012Metric_Pad1.18x1.45mm_HandSolder_C9_HandSolder | HandSolder:C_0805_2012Metric_Pad1.18x1.45mm_HandSolder_C10_HandSolder | HandSolder:C_0805_2012Metric_Pad1.18x1.45mm_HandSolder_C33_HandSolder,B,https://www.murata.com/en-global/products/productdetail?part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 | https://www.murata.com/
GRM155R71H104KE14D,Murata,9,C15 C16 C20 C27 C29 C32 C35 C36 C48,100nF 50V X7R,HandSolder:C_0402_1005Metric_Pad0.74x0.62mm_HandSolder_C15_HandSolder | HandSolder:C_0402_1005Metric_Pad0.74x0.62mm_HandSolder_C16_HandSolder | HandSolder:C_0402_1005Metric_Pad0.74x0.62mm_HandSolder_C20_HandSolder | HandSolder:C_0402_1005Metric_Pad0.74x0.62mm_HandSolder_C27_HandSolder | HandSolder:C_0402_1005Metric_Pad0.74x0.62mm_HandSolder_C29_HandSolder | HandSolder:C_0402_1005Metric_Pad0.74x0.62mm_HandSolder_C32_HandSolder | HandSolder:C_0402_1005Metric_Pad0.74x0.62mm_HandSolder_C35_HandSolder | HandSolder:C_0402_1005Metric_Pad0.74x0.62mm_HandSolder_C36_HandSolder | HandSolder:C_0402_1005Metric_Pad0.74x0.62mm_HandSolder_C48_HandSolder,B | F,https://search.murata.co.jp/Ceramy/image/img/A01X/G101/ENG/G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 | https://product.tdk.com/en/search/capacitor/ceramic/mlcc/inf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 | https://www.murata.com/
GRM188R61A106ME69D,Murata,1,C17,10uF 10V X5R 20%,HandSolder:C_0603_1608Metric_Pad1.08x0.95mm_HandSolder_C17_HandSolder,B,https://search.murata.co.jp/Ceramy/image/img/A01X/G101/ENG/G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
C1005X7R1H104K050BB,TDK,3,C24 C25 C26,100nF 50V X7R,HandSolder:C_0402_1005Metric_Pad0.74x0.62mm_HandSolder_C24_HandSolder | HandSolder:C_0402_1005Metric_Pad0.74x0.62mm_HandSolder_C25_HandSolder | HandSolder:C_0402_1005Metric_Pad0.74x0.62mm_HandSolder_C26_HandSolder,B | F,https://product.tdk.com/en/search/capacitor/ceramic/mlcc/inf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
GRM155R71H472KA01D,Murata,1,C30,4.7nF 50V X7R 10%,Sourced:C_0402_1005Metric,F,https://search.murata.co.jp/Ceramy/image/img/A01X/G101/ENG/G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
GRM1555C1H102JA01D,Murata,1,C31,1nF 50V C0G,HandSolder:C_0402_1005Metric_Pad0.74x0.62mm_HandSolder_C31_HandSolder,B,https://www.murata.com/
T520D337M006ATE025,KEMET,1,C37,330uF 6.3V polymer,HandSolder:CP_EIA-7343-31_Kemet-D_C37_HandSolder,F,https://docs.rs-online.com/885c/A700000006401849.pdf
CL05A105KP5NNNC,Samsung Electro-Mechanics,6,C38 C39 C40 C41 C42 C43,1uF 10V X5R,HandSolder:C_0402_1005Metric_Pad0.74x0.62mm_HandSolder_C38_HandSolder | HandSolder:C_0402_1005Metric_Pad0.74x0.62mm_HandSolder_C39_HandSolder | HandSolder:C_0402_1005Metric_Pad0.74x0.62mm_HandSolder_C40_HandSolder | HandSolder:C_0402_1005Metric_Pad0.74x0.62mm_HandSolder_C41_HandSolder | HandSolder:C_0402_1005Metric_Pad0.74x0.62mm_HandSolder_C42_HandSolder | HandSolder:C_0402_1005Metric_Pad0.74x0.62mm_HandSolder_C43_HandSolder,F,https://product.samsungsem.com/mlcc/CL05A105KP5NNN.do
GRM155R61A474KE15D,Murata,1,C44,470nF 10V X5R,Sourced:C_0402_1005Metric,F,https://www.murata.com/
CL10A225KP8NNNC,Samsung Electro-Mechanics,1,C45,2.2uF 10V X5R,Sourced:C_0603_1608Metric,F,https://product.samsungsem.com/mlcc/CL10A225KP8NNN.do
T530X687M006ATE010,KEMET,2,C46 C47,680uF 6.3V polymer,HandSolder:CP_EIA-7343-43_Kemet-X_C46_HandSolder | HandSolder:CP_EIA-7343-43_Kemet-X_C47_HandSolder,F,https://search.kemet.com/download/specsheet/T530X687M006ATE010
T520D477M006ATE025,KEMET,1,C50,470uF 6.3V polymer,HandSolder:CP_EIA-7343-31_Kemet-D_C50_HandSolder,B,https://www.digikey.com/en/products/detail/kemet/T520D477M00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
"PMEG2010ER,115",Nexperia,1,D1,PMEG2010ER flyback,HandSolder:D_Diode_SMD_Nexperia_CFP3_SOD-123W_D1_HandSolder,B,https://assets.nexperia.com/documents/data-sheet/PMEG2010ER.pdf
LTST-C190KRKT,Lite-On,1,D2,CHARGE LED,HandSolder:LED_0603_1608Metric_Pad1.05x0.95mm_HandSolder_D2_HandSolder,F,
TYPE-C-31-M-12,HRO,1,J1,USB-C USB2.0,HandSolder:USB_C_Receptacle_HRO_TYPE-C-31-M-12_J1_HandSolder,F,https://www.usb.org/sites/default/files/documents/usb_type-c.zip
S2B-PH-SM4-TB(LF)(SN),JST,1,J2,BATTERY DTP803040,Sourced:Connector_JST_JST_PH_S2B-PH-SM4-TB_1x02-1MP_P2.00mm_Horizontal,F,
SM08B-SRSS-TB(LF)(SN),JST,1,J3,ST7789 HARNESS,Connector_HandSolder:Connector_JST_JST_SH_SM08B-SRSS-TB_1x08_1MP_P1.00mm_Horizontal_J3_HandSolder,F,
DM3AT-SF-PEJM5,Hirose,1,J10,microSD DM3AT-SF-PEJM5,HandSolder:microSD_HC_Hirose_DM3AT-SF-PEJM5_J10_HandSolder,B,https://www.hirose.com/en/product/p/CL0609-0031-0-00
PJ-320D-4A,Korean Hroparts Elec,1,J11,3.5mm stereo output,Sourced:AUDIO-SMD_PJ-320D,B,https://www.lcsc.com/product-detail/C95562.html
XFL4020-222MEC,Coilcraft,1,L1,2.2uH XFL4020,HandSolder:Inductor_SMD_L_Coilcraft_XxL4020_L1_HandSolder,B,https://www.coilcraft.com/getmedia/50632d43-da1b-4cdb-8ab4-3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
AO3400A,Alpha & Omega Semiconductor,1,Q1,AO3400A,HandSolder:SOT-23_Handsoldering_Q1_HandSolder,B,http://www.aosmd.com/pdfs/datasheet/AO3400A.pdf
2N7002,Nexperia,2,Q2 Q4,2N7002,HandSolder:SOT-23_Handsoldering_Q2_HandSolder | HandSolder:SOT-23_Handsoldering_Q4_HandSolder,B | F,https://assets.nexperia.com/documents/data-sheet/2N7002.pdf
AO3401A,Alpha & Omega Semiconductor,1,Q3,AO3401A,HandSolder:SOT-23_Handsoldering_Q3_HandSolder,B,https://www.aosmd.com/res/data_sheets/AO3401A.pdf
RC0402FR-07100KL,Yageo,16,R1 R11 R35 R39 R40 R42 R43 R44 R49 R50 R51 R53 R56 R57 R58 R62,100k 1%,HandSolder:R_0402_1005Metric_Pad0.72x0.64mm_HandSolder_R1_HandSolder | HandSolder:R_0402_1005Metric_Pad0.72x0.64mm_HandSolder_R11_HandSolder | Sourced:Resistor_SMD_R_0402_1005Metric | HandSolder:R_0402_1005Metric_Pad0.72x0.64mm_HandSolder_R39_HandSolder | HandSolder:R_0402_1005Metric_Pad0.72x0.64mm_HandSolder_R40_HandSolder | HandSolder:R_0402_1005Metric_Pad0.72x0.64mm_HandSolder_R42_HandSolder | HandSolder:R_0402_1005Metric_Pad0.72x0.64mm_HandSolder_R43_HandSolder | HandSolder:R_0402_1005Metric_Pad0.72x0.64mm_HandSolder_R44_HandSolder | HandSolder:R_0402_1005Metric_Pad0.72x0.64mm_HandSolder_R49_HandSolder | HandSolder:R_0402_1005Metric_Pad0.72x0.64mm_HandSolder_R50_HandSolder | HandSolder:R_0402_1005Metric_Pad0.72x0.64mm_HandSolder_R51_HandSolder | HandSolder:R_0402_1005Metric_Pad0.72x0.64mm_HandSolder_R53_HandSolder | HandSolder:R_0402_1005Metric_Pad0.72x0.64mm_HandSolder_R56_HandSolder | HandSolder:R_0402_1005Metric_Pad0.72x0.64mm_HandSolder_R57_HandSolder | Sourced:R_0402_1005Metric | HandSolder:R_0402_1005Metric_Pad0.72x0.64mm_HandSolder_R62_HandSolder,B | F,https://www.yageo.com/en/Product/Index/RC | https://www.yageo.com/
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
